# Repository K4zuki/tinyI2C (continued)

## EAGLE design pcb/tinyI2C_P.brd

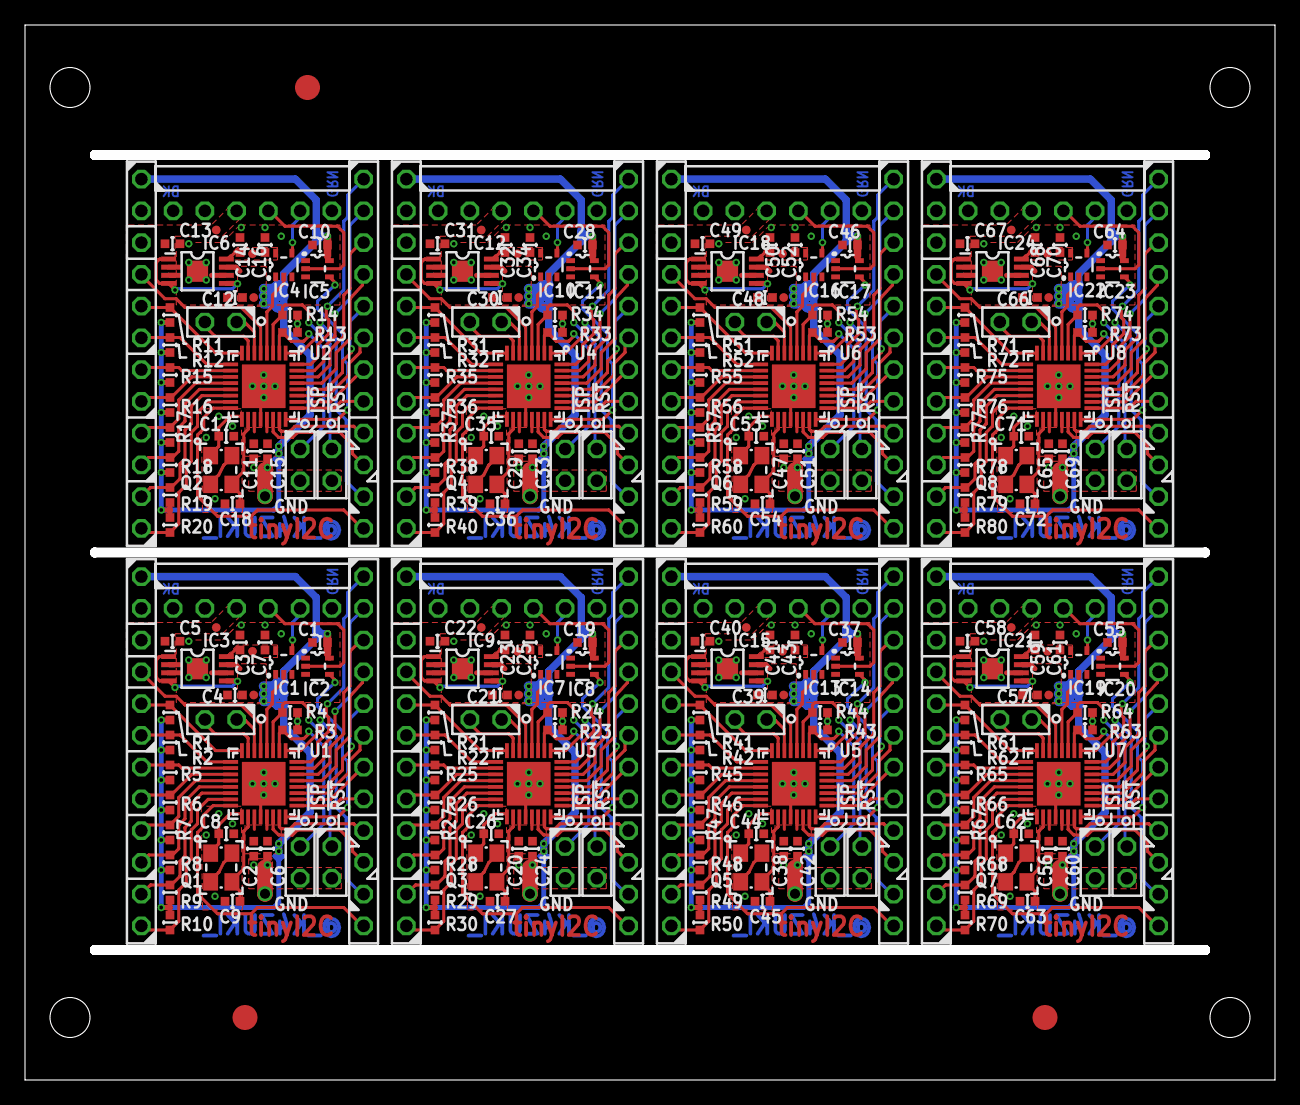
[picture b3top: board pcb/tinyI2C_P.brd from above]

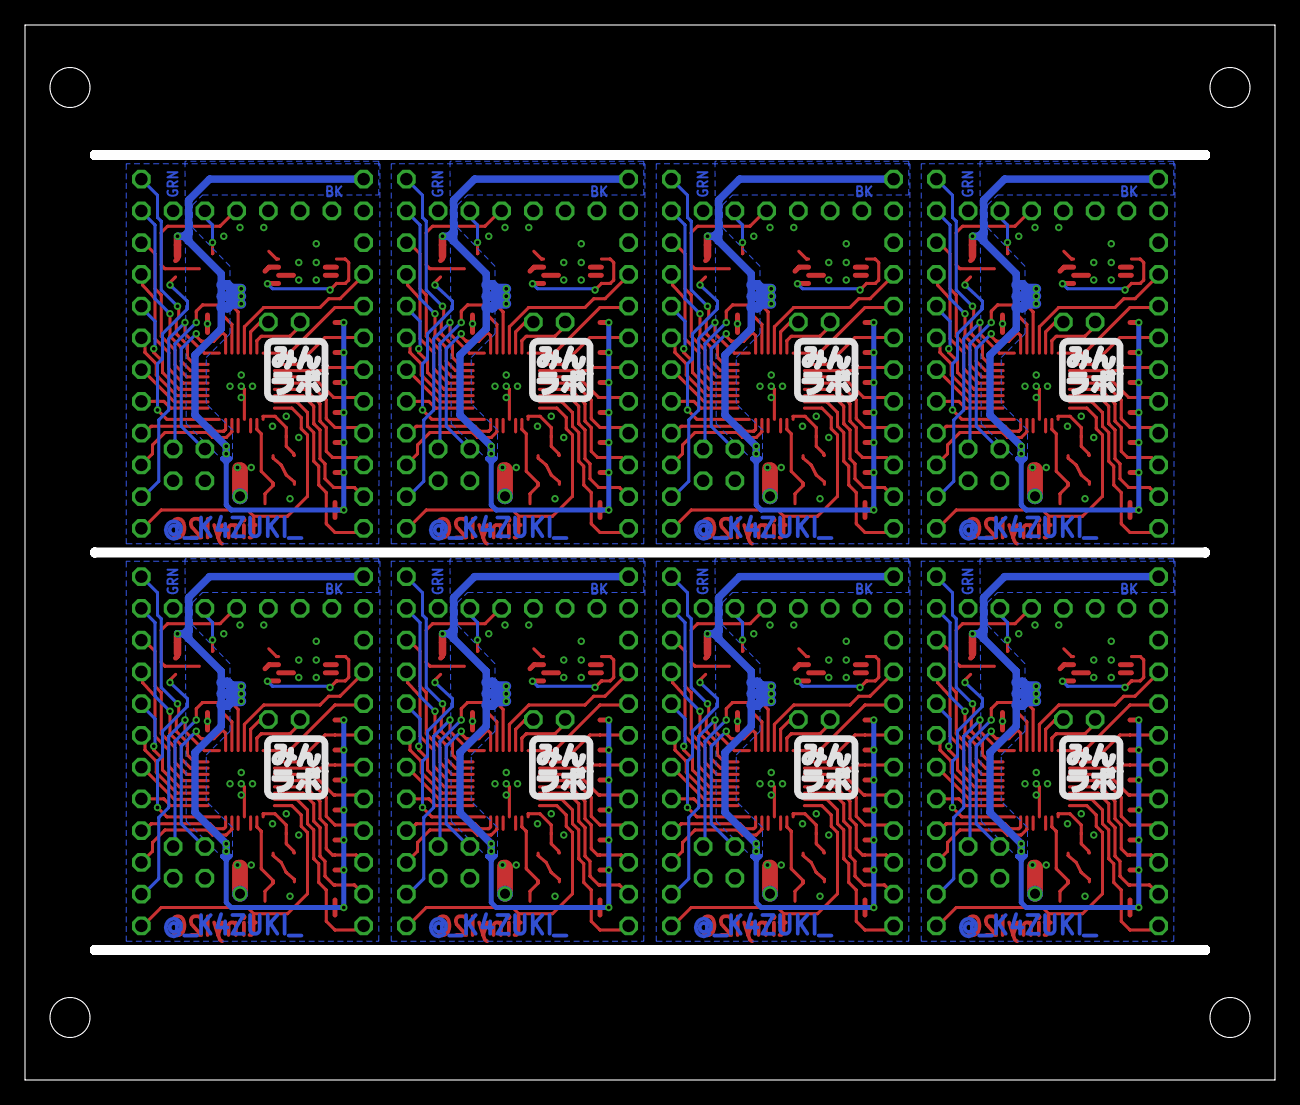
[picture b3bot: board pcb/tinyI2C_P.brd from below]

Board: 2 copper layers, 100.0 x 84.4 mm, 291 parts (16 on the bottom side), 280 nets.

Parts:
C1, C2, C6, C7, C10, C11, C15, C16, C19, C20, C24, C25, C28, C29, C33, C34, C37, C38, C42, C43, C46, C47, C51, C52, C55, C56, C60, C61, C64, C65, C69, C70: 0.1u/1005; C0402
C3, C4, C5, C12, C13, C14, C21, C22, C23, C30, C31, C32, C39, C40, C41, C48, C49, C50, C57, C58, C59, C66, C67, C68: 10u/1005; C0402
C8, C9, C17, C18, C26, C27, C35, C36, C44, C45, C53, C54, C62, C63, C71, C72: 18p/1005; C0402
I1, I2, I3, I4, I5, I6, I7, I8: ICON_MINLAB_5.2S; ICON_MINLAB_5.2MM
IC1, IC2, IC4, IC5, IC7, IC8, IC10, IC11, IC13, IC14, IC16, IC17, IC19, IC20, IC22, IC23: 74LVC1G125DCK; SC70-5
IC3, IC6, IC9, IC12, IC15, IC18, IC21, IC24: IC_LDO_MIC5355; IC_08_0.65_160MIL_EP
Q1, Q2, Q3, Q4, Q5, Q6, Q7, Q8: 12MHz; NX3225
R1, R2, R11, R12, R21, R22, R31, R32, R41, R42, R51, R52, R61, R62, R71, R72: 220/1005; C0402
R3, R4, R5, R6, R7, R8, R9, R10, R13, R14, R15, R16, R17, R18, R19, R20, R23, R24, R25, R26, R27, R28, R29, R30, R33, R34, R35, R36, R37, R38, R39, R40, R43, R44, R45, R46, R47, R48, R49, R50, R53, R54, R55, R56, R57, R58, R59, R60, R63, R64, R65, R66, R67, R68, R69, R70, R73, R74, R75, R76, R77, R78, R79, R80: 10k/1005; C0402
TP1, TP2, TP6, TP9, TP10, TP12, TP14, TP15, TP17, TP19, TP20, TP22, TP24, TP25, TP27, TP29, TP30, TP32, TP34, TP35, TP37, TP39, TP40, TP42: TPTP07R; TP07R
TP3, TP7, TP11, TP13, TP16, TP18, TP21, TP23, TP26, TP28, TP31, TP33, TP36, TP38, TP41, TP43: TPB1,27; B1,27
TP4, TP5, TP8: TPTP20R; TP20R
U1, U2, U3, U4, U5, U6, U7, U8: LPC824M201JHI33; HVQFN33
X1, X2, X8, X9, X14, X15, X20, X21, X26, X27, X32, X33, X38, X39, X44, X45: TSW-112-02-S-S
X3, X7, X13, X19, X25, X31, X37, X43: TSW-106-02-S-S-RA
X4, X5, X6, X10, X11, X12, X16, X17, X18, X22, X23, X24, X28, X29, X30, X34, X35, X36, X40, X41, X42, X46, X47, X48: TSW-102-02-S-S

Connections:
1.8V: C1.1, C2.1, C4.1, C6.1, IC2.5, IC3.7, R1.2, R2.2, R3.2, R4.2, R5.2, R6.2, R7.2, R8.2, R9.2, R10.2, TP2.TP, U1.19, U1.21, X1.1
1.8V1: C10.1, C11.1, C12.1, C15.1, IC5.5, IC6.7, R11.2, R12.2, R13.2, R14.2, R15.2, R16.2, R17.2, R18.2, R19.2, R20.2, TP10.TP, U2.19, U2.21, X8.1
1.8V2: C19.1, C20.1, C21.1, C24.1, IC8.5, IC9.7, R21.2, R22.2, R23.2, R24.2, R25.2, R26.2, R27.2, R28.2, R29.2, R30.2, TP15.TP, U3.19, U3.21, X14.1
1.8V3: C28.1, C29.1, C30.1, C33.1, IC11.5, IC12.7, R31.2, R32.2, R33.2, R34.2, R35.2, R36.2, R37.2, R38.2, R39.2, R40.2, TP20.TP, U4.19, U4.21, X20.1
1.8V4: C37.1, C38.1, C39.1, C42.1, IC14.5, IC15.7, R41.2, R42.2, R43.2, R44.2, R45.2, R46.2, R47.2, R48.2, R49.2, R50.2, TP25.TP, U5.19, U5.21, X26.1
1.8V5: C46.1, C47.1, C48.1, C51.1, IC17.5, IC18.7, R51.2, R52.2, R53.2, R54.2, R55.2, R56.2, R57.2, R58.2, R59.2, R60.2, TP30.TP, U6.19, U6.21, X32.1
1.8V6: C55.1, C56.1, C57.1, C60.1, IC20.5, IC21.7, R61.2, R62.2, R63.2, R64.2, R65.2, R66.2, R67.2, R68.2, R69.2, R70.2, TP35.TP, U7.19, U7.21, X38.1
1.8V7: C64.1, C65.1, C66.1, C69.1, IC23.5, IC24.7, R71.2, R72.2, R73.2, R74.2, R75.2, R76.2, R77.2, R78.2, R79.2, R80.2, TP40.TP, U8.19, U8.21, X44.1
3.3V: C3.1, C7.1, IC1.5, IC3.8, TP6.TP
3.3V1: C14.1, C16.1, IC4.5, IC6.8, TP12.TP
3.3V2: C23.1, C25.1, IC7.5, IC9.8, TP17.TP
3.3V3: C32.1, C34.1, IC10.5, IC12.8, TP22.TP
3.3V4: C41.1, C43.1, IC13.5, IC15.8, TP27.TP
3.3V5: C50.1, C52.1, IC16.5, IC18.8, TP32.TP
3.3V6: C59.1, C61.1, IC19.5, IC21.8, TP37.TP
3.3V7: C68.1, C70.1, IC22.5, IC24.8, TP42.TP
5V: C5.1, IC3.1, IC3.4, IC3.5, TP1.TP, X1.3, X3.3
5V1: C13.1, IC6.1, IC6.4, IC6.5, TP9.TP, X7.3, X8.3
5V2: C22.1, IC9.1, IC9.4, IC9.5, TP14.TP, X13.3, X14.3
5V3: C31.1, IC12.1, IC12.4, IC12.5, TP19.TP, X19.3, X20.3
5V4: C40.1, IC15.1, IC15.4, IC15.5, TP24.TP, X25.3, X26.3
5V5: C49.1, IC18.1, IC18.4, IC18.5, TP29.TP, X31.3, X32.3
5V6: C58.1, IC21.1, IC21.4, IC21.5, TP34.TP, X37.3, X38.3
5V7: C67.1, IC24.1, IC24.4, IC24.5, TP39.TP, X43.3, X44.3
!ISP!: R3.1, U1.2, X6.1
!ISP!1: R13.1, U2.2, X12.1
!ISP!2: R23.1, U3.2, X18.1
!ISP!3: R33.1, U4.2, X24.1
!ISP!4: R43.1, U5.2, X30.1
!ISP!5: R53.1, U6.2, X36.1
!ISP!6: R63.1, U7.2, X42.1
!ISP!7: R73.1, U8.2, X48.1
!RESET!: R4.1, U1.3, X4.1
!RESET!1: R14.1, U2.3, X10.1
!RESET!2: R24.1, U3.3, X16.1
!RESET!3: R34.1, U4.3, X22.1
!RESET!4: R44.1, U5.3, X28.1
!RESET!5: R54.1, U6.3, X34.1
!RESET!6: R64.1, U7.3, X40.1
!RESET!7: R74.1, U8.3, X46.1
GND: C1.2, C2.2, C3.2, C4.2, C5.2, C6.2, C7.2, C8.2, C9.2, IC1.1, IC1.3, IC2.1, IC2.3, IC3.2, IC3.3, IC3.6, IC3.EXP, Q1.2, Q1.4, TP3.TP, TP7.TP, U1.20, U1.EXP, X1.2, X3.1, X4.2, X6.2
GND1: C10.2, C11.2, C12.2, C13.2, C14.2, C15.2, C16.2, C17.2, C18.2, IC4.1, IC4.3, IC5.1, IC5.3, IC6.2, IC6.3, IC6.6, IC6.EXP, Q2.2, Q2.4, TP11.TP, TP13.TP, U2.20, U2.EXP, X7.1, X8.2, X10.2, X12.2
GND2: C19.2, C20.2, C21.2, C22.2, C23.2, C24.2, C25.2, C26.2, C27.2, IC7.1, IC7.3, IC8.1, IC8.3, IC9.2, IC9.3, IC9.6, IC9.EXP, Q3.2, Q3.4, TP16.TP, TP18.TP, U3.20, U3.EXP, X13.1, X14.2, X16.2, X18.2
GND3: C28.2, C29.2, C30.2, C31.2, C32.2, C33.2, C34.2, C35.2, C36.2, IC10.1, IC10.3, IC11.1, IC11.3, IC12.2, IC12.3, IC12.6, IC12.EXP, Q4.2, Q4.4, TP21.TP, TP23.TP, U4.20, U4.EXP, X19.1, X20.2, X22.2, X24.2
GND4: C37.2, C38.2, C39.2, C40.2, C41.2, C42.2, C43.2, C44.2, C45.2, IC13.1, IC13.3, IC14.1, IC14.3, IC15.2, IC15.3, IC15.6, IC15.EXP, Q5.2, Q5.4, TP26.TP, TP28.TP, U5.20, U5.EXP, X25.1, X26.2, X28.2, X30.2
GND5: C46.2, C47.2, C48.2, C49.2, C50.2, C51.2, C52.2, C53.2, C54.2, IC16.1, IC16.3, IC17.1, IC17.3, IC18.2, IC18.3, IC18.6, IC18.EXP, Q6.2, Q6.4, TP31.TP, TP33.TP, U6.20, U6.EXP, X31.1, X32.2, X34.2, X36.2
GND6: C55.2, C56.2, C57.2, C58.2, C59.2, C60.2, C61.2, C62.2, C63.2, IC19.1, IC19.3, IC20.1, IC20.3, IC21.2, IC21.3, IC21.6, IC21.EXP, Q7.2, Q7.4, TP36.TP, TP38.TP, U7.20, U7.EXP, X37.1, X38.2, X40.2, X42.2
GND7: C64.2, C65.2, C66.2, C67.2, C68.2, C69.2, C70.2, C71.2, C72.2, IC22.1, IC22.3, IC23.1, IC23.3, IC24.2, IC24.3, IC24.6, IC24.EXP, Q8.2, Q8.4, TP41.TP, TP43.TP, U8.20, U8.EXP, X43.1, X44.2, X46.2, X48.2
GPIO00: U1.32, X2.1
GPIO01: U1.31, X2.2
GPIO02: U1.30, X2.3
GPIO03: U1.29, X2.4
GPIO04: U1.28, X2.5
GPIO05: U1.27, X2.6
GPIO06: U1.26, X2.7
GPIO07: U1.25, X2.8
GPIO08: U2.5, X8.4
GPIO09: R15.1, U2.10, X8.7
GPIO10: R10.1, U1.15, X1.12
GPIO11: R9.1, U1.14, X1.11
GPIO12: R8.1, U1.13, X1.10
GPIO13: R7.1, U1.12, X1.9
GPIO14: R6.1, U1.11, X1.8
GPIO15: R5.1, U1.10, X1.7
GPIO16: U1.5, X1.4
GPIO17: R16.1, U2.11, X8.8
GPIO18: R17.1, U2.12, X8.9
GPIO19: R18.1, U2.13, X8.10
GPIO20: R19.1, U2.14, X8.11
GPIO21: R20.1, U2.15, X8.12
GPIO22: U2.25, X9.8
GPIO23: U2.26, X9.7
GPIO24: U2.27, X9.6
GPIO25: U2.28, X9.5
GPIO26: U2.29, X9.4
GPIO27: U2.30, X9.3
GPIO28: U2.31, X9.2
GPIO29: U2.32, X9.1
GPIO30: U3.5, X14.4
GPIO31: R25.1, U3.10, X14.7
GPIO32: R26.1, U3.11, X14.8
GPIO33: R27.1, U3.12, X14.9
GPIO34: R28.1, U3.13, X14.10
GPIO35: R29.1, U3.14, X14.11
GPIO36: R30.1, U3.15, X14.12
GPIO37: U3.25, X15.8
GPIO38: U3.26, X15.7
GPIO39: U3.27, X15.6
GPIO40: U3.28, X15.5
GPIO41: U3.29, X15.4
GPIO42: U3.30, X15.3
GPIO43: U3.31, X15.2
GPIO44: U3.32, X15.1
GPIO45: U4.5, X20.4
GPIO46: R35.1, U4.10, X20.7
GPIO47: R36.1, U4.11, X20.8
GPIO48: R37.1, U4.12, X20.9
GPIO49: R38.1, U4.13, X20.10
GPIO50: R39.1, U4.14, X20.11
GPIO51: R40.1, U4.15, X20.12
GPIO52: U4.25, X21.8
GPIO53: U4.26, X21.7
GPIO54: U4.27, X21.6
GPIO55: U4.28, X21.5
GPIO56: U4.29, X21.4
GPIO57: U4.30, X21.3
GPIO58: U4.31, X21.2
GPIO59: U4.32, X21.1
GPIO60: U5.5, X26.4
GPIO61: R45.1, U5.10, X26.7
GPIO62: R46.1, U5.11, X26.8
GPIO63: R47.1, U5.12, X26.9
GPIO64: R48.1, U5.13, X26.10
GPIO65: R49.1, U5.14, X26.11
GPIO66: R50.1, U5.15, X26.12
GPIO67: U5.25, X27.8
GPIO68: U5.26, X27.7
GPIO69: U5.27, X27.6
GPIO70: U5.28, X27.5
GPIO71: U5.29, X27.4
GPIO72: U5.30, X27.3
GPIO73: U5.31, X27.2
GPIO74: U5.32, X27.1
GPIO75: U6.5, X32.4
GPIO76: R55.1, U6.10, X32.7
GPIO77: R56.1, U6.11, X32.8
GPIO78: R57.1, U6.12, X32.9
GPIO79: R58.1, U6.13, X32.10
GPIO80: R59.1, U6.14, X32.11
GPIO81: R60.1, U6.15, X32.12
GPIO82: U6.25, X33.8
GPIO83: U6.26, X33.7
GPIO84: U6.27, X33.6
GPIO85: U6.28, X33.5
GPIO86: U6.29, X33.4
GPIO87: U6.30, X33.3
GPIO88: U6.31, X33.2
GPIO89: U6.32, X33.1
GPIO90: U7.5, X38.4
GPIO91: R65.1, U7.10, X38.7
GPIO92: R66.1, U7.11, X38.8
GPIO93: R67.1, U7.12, X38.9
GPIO94: R68.1, U7.13, X38.10
GPIO95: R69.1, U7.14, X38.11
GPIO96: R70.1, U7.15, X38.12
GPIO97: U7.25, X39.8
GPIO98: U7.26, X39.7
GPIO99: U7.27, X39.6
GPIO100: U7.28, X39.5
GPIO101: U7.29, X39.4
GPIO102: U7.30, X39.3
GPIO103: U7.31, X39.2
GPIO104: U7.32, X39.1
GPIO105: U8.5, X44.4
GPIO106: R75.1, U8.10, X44.7
GPIO107: R76.1, U8.11, X44.8
GPIO108: R77.1, U8.12, X44.9
GPIO109: R78.1, U8.13, X44.10
GPIO110: R79.1, U8.14, X44.11
GPIO111: R80.1, U8.15, X44.12
GPIO112: U8.25, X45.8
GPIO113: U8.26, X45.7
GPIO114: U8.27, X45.6
GPIO115: U8.28, X45.5
GPIO116: U8.29, X45.4
GPIO117: U8.30, X45.3
GPIO118: U8.31, X45.2
GPIO119: U8.32, X45.1
I2C_SCL: R2.1, U1.9, X1.6
I2C_SCL1: R12.1, U2.9, X8.6
I2C_SCL2: R22.1, U3.9, X14.6
I2C_SCL3: R32.1, U4.9, X20.6
I2C_SCL4: R42.1, U5.9, X26.6
I2C_SCL5: R52.1, U6.9, X32.6
I2C_SCL6: R62.1, U7.9, X38.6
I2C_SCL7: R72.1, U8.9, X44.6
I2C_SDA: R1.1, U1.8, X1.5
I2C_SDA1: R11.1, U2.8, X8.5
I2C_SDA2: R21.1, U3.8, X14.5
I2C_SDA3: R31.1, U4.8, X20.5
I2C_SDA4: R41.1, U5.8, X26.5
I2C_SDA5: R51.1, U6.8, X32.5
I2C_SDA6: R61.1, U7.8, X38.5
I2C_SDA7: R71.1, U8.8, X44.5
unnamed: C8.1, Q1.1, U1.17
unnamed: C17.1, Q2.1, U2.17
unnamed: C9.1, Q1.3, U1.18
unnamed: C18.1, Q2.3, U2.18
unnamed: C26.1, Q3.1, U3.17
unnamed: C27.1, Q3.3, U3.18
unnamed: C35.1, Q4.1, U4.17
unnamed: C36.1, Q4.3, U4.18
unnamed: C44.1, Q5.1, U5.17
unnamed: C45.1, Q5.3, U5.18
unnamed: C53.1, Q6.1, U6.17
unnamed: C54.1, Q6.3, U6.18
unnamed: C62.1, Q7.1, U7.17
unnamed: C63.1, Q7.3, U7.18
unnamed: C71.1, Q8.1, U8.17
unnamed: C72.1, Q8.3, U8.18
RX<-: IC1.4, X3.5
RX<-1: IC4.4, X7.5
RX<-2: IC7.4, X13.5
RX<-3: IC10.4, X19.5
RX<-4: IC13.4, X25.5
RX<-5: IC16.4, X31.5
RX<-6: IC19.4, X37.5
RX<-7: IC22.4, X43.5
SPI_CS: U1.16, X2.12
SPI_CS1: U2.16, X9.12
SPI_CS2: U3.16, X15.12
SPI_CS3: U4.16, X21.12
SPI_CS4: U5.16, X27.12
SPI_CS5: U6.16, X33.12
SPI_CS6: U7.16, X39.12
SPI_CS7: U8.16, X45.12
SPI_MISO: U1.22, X2.10
SPI_MISO1: U2.22, X9.10
SPI_MISO2: U3.22, X15.10
SPI_MISO3: U4.22, X21.10
SPI_MISO4: U5.22, X27.10
SPI_MISO5: U6.22, X33.10
SPI_MISO6: U7.22, X39.10
SPI_MISO7: U8.22, X45.10
SPI_MOSI: U1.23, X2.9
SPI_MOSI1: U2.23, X9.9
SPI_MOSI2: U3.23, X15.9
SPI_MOSI3: U4.23, X21.9
SPI_MOSI4: U5.23, X27.9
SPI_MOSI5: U6.23, X33.9
SPI_MOSI6: U7.23, X39.9
SPI_MOSI7: U8.23, X45.9
SPI_SCK: U1.1, X2.11
SPI_SCK1: U2.1, X9.11
SPI_SCK2: U3.1, X15.11
SPI_SCK3: U4.1, X21.11
SPI_SCK4: U5.1, X27.11
SPI_SCK5: U6.1, X33.11
SPI_SCK6: U7.1, X39.11
SPI_SCK7: U8.1, X45.11
SWCLK: U1.6, X5.1
SWCLK1: U2.6, X11.1
SWCLK2: U3.6, X17.1
SWCLK3: U4.6, X23.1
SWCLK4: U5.6, X29.1
SWCLK5: U6.6, X35.1
SWCLK6: U7.6, X41.1
SWCLK7: U8.6, X47.1
SWDIO: U1.7, X5.2
SWDIO1: U2.7, X11.2
SWDIO2: U3.7, X17.2
SWDIO3: U4.7, X23.2
SWDIO4: U5.7, X29.2
SWDIO5: U6.7, X35.2
SWDIO6: U7.7, X41.2
SWDIO7: U8.7, X47.2
TGT_RX: IC2.4, U1.24
TGT_RX1: IC5.4, U2.24
TGT_RX2: IC8.4, U3.24
TGT_RX3: IC11.4, U4.24
TGT_RX4: IC14.4, U5.24
TGT_RX5: IC17.4, U6.24
TGT_RX6: IC20.4, U7.24
TGT_RX7: IC23.4, U8.24
TGT_TX: IC1.2, U1.4
TGT_TX1: IC4.2, U2.4
TGT_TX2: IC7.2, U3.4
TGT_TX3: IC10.2, U4.4
TGT_TX4: IC13.2, U5.4
TGT_TX5: IC16.2, U6.4
TGT_TX6: IC19.2, U7.4
TGT_TX7: IC22.2, U8.4
TX->: IC2.2, X3.4
TX->1: IC5.2, X7.4
TX->2: IC8.2, X13.4
TX->3: IC11.2, X19.4
TX->4: IC14.2, X25.4
TX->5: IC17.2, X31.4
TX->6: IC20.2, X37.4
TX->7: IC23.2, X43.4

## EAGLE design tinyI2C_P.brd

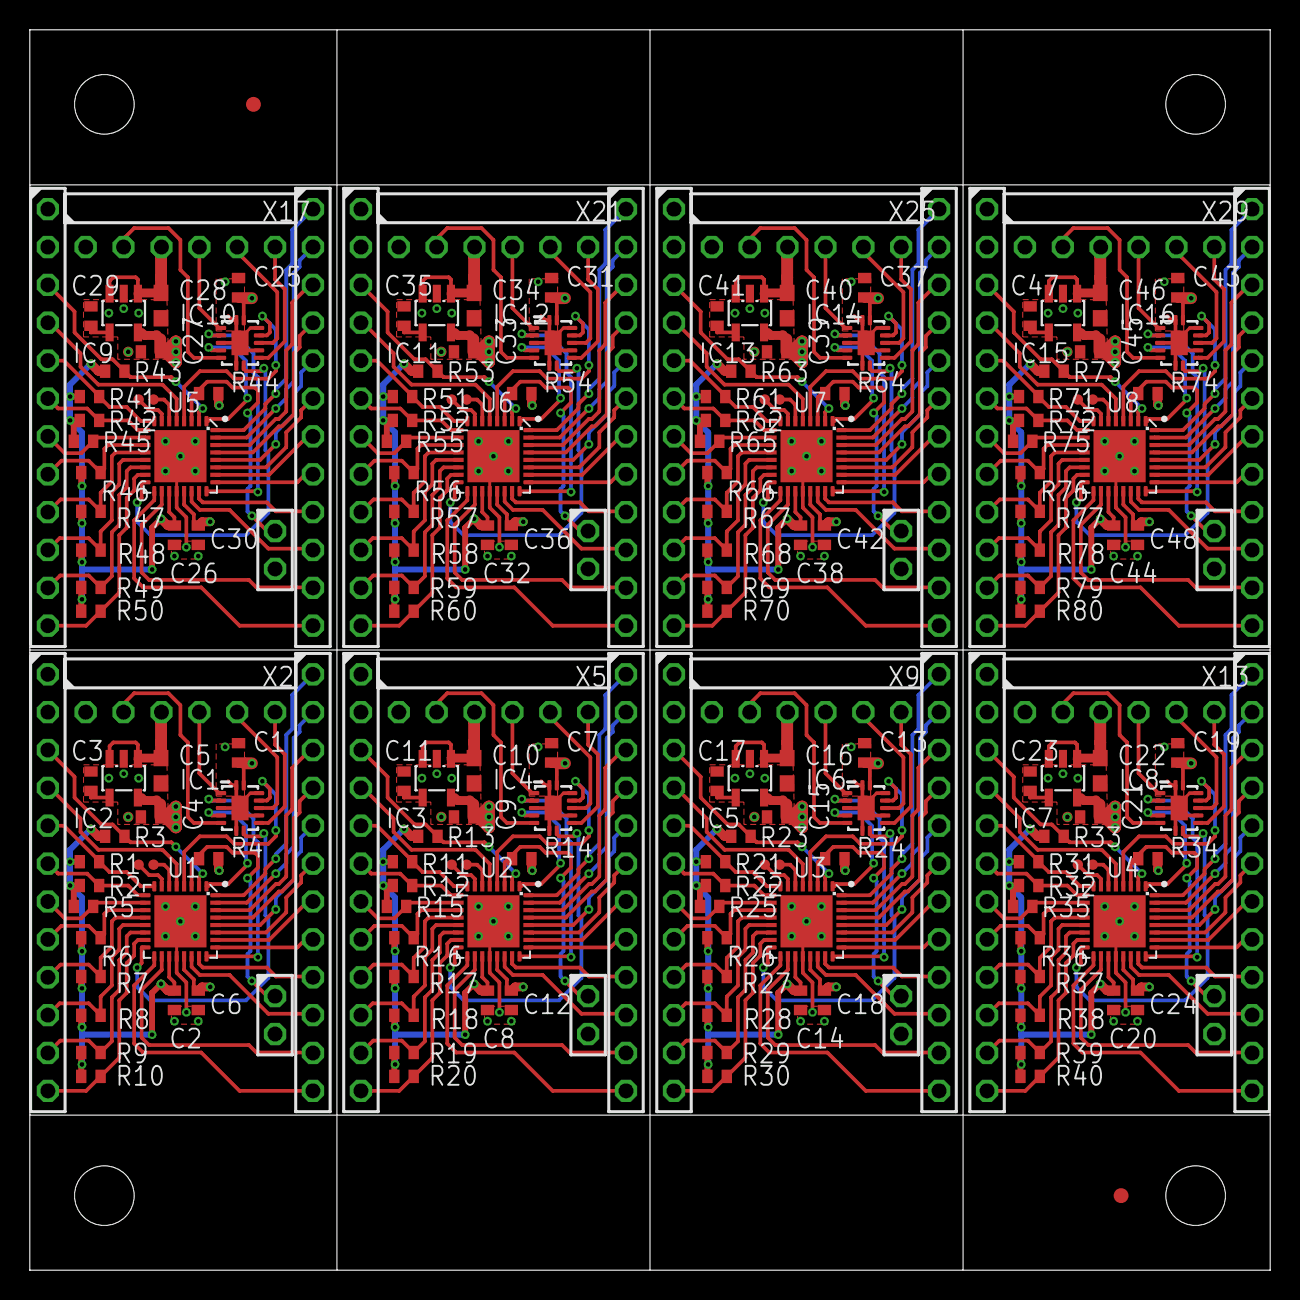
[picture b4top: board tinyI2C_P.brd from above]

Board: 2 copper layers, 83.2 x 83.2 mm, 226 parts (0 on the bottom side), 296 nets.

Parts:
C1, C2, C3, C4, C6, C7, C8, C9, C11, C12, C13, C14, C15, C17, C18, C19, C20, C21, C23, C24, C25, C26, C27, C29, C30, C31, C32, C33, C35, C36, C37, C38, C39, C41, C42, C43, C44, C45, C47, C48: 1005; C1005
C5, C10, C16, C22, C28, C34, C40, C46: 1608; C1608
IC1, IC4, IC6, IC8, IC10, IC12, IC14, IC16: 74ABT125BQ; DHVQFN14
IC2, IC3, IC5, IC7, IC9, IC11, IC13, IC15: TPS76318; SOT23-DBV
R1, R2, R11, R12, R21, R22, R31, R32, R41, R42, R51, R52, R61, R62, R71, R72: 220/1005; R1005
R3, R4, R5, R6, R7, R8, R9, R10, R13, R14, R15, R16, R17, R18, R19, R20, R23, R24, R25, R26, R27, R28, R29, R30, R33, R34, R35, R36, R37, R38, R39, R40, R43, R44, R45, R46, R47, R48, R49, R50, R53, R54, R55, R56, R57, R58, R59, R60, R63, R64, R65, R66, R67, R68, R69, R70, R73, R74, R75, R76, R77, R78, R79, R80: 10k/1005; R1005
TP1, TP2, TP3, TP6, TP7, TP8, TP9, TP10, TP11, TP12, TP13, TP14, TP15, TP16, TP17, TP18, TP19, TP20, TP21, TP22, TP23, TP24, TP25, TP26, TP27, TP28, TP29, TP30, TP31, TP32, TP33, TP34, TP35, TP36, TP37, TP38, TP39, TP40, TP41, TP42: TPTP07R; TP07R
TP4, TP5: TPTP10R; TP10R
U1, U2, U3, U4, U5, U6, U7, U8: LPC824M201JHI33; HVQFN33
X1, X3, X6, X7, X10, X11, X14, X15, X18, X19, X22, X23, X26, X27, X30, X31: TSW-112-02-S-S
X2, X5, X9, X13, X17, X21, X25, X29: TSW-106-02-S-S-RA
X4, X8, X12, X16, X20, X24, X28, X32: TSW-102-02-S-S

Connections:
1.8V: C1.1, C2.1, C4.1, C6.1, IC1.14, IC2.5, R1.2, R2.2, R3.2, R4.2, R5.2, R6.2, R7.2, R8.2, R9.2, R10.2, TP2.TP, U1.19, U1.21, X1.1
1.8V1: C7.1, C8.1, C9.1, C12.1, IC3.5, IC4.14, R11.2, R12.2, R13.2, R14.2, R15.2, R16.2, R17.2, R18.2, R19.2, R20.2, TP7.TP, U2.19, U2.21, X6.1
1.8V2: C13.1, C14.1, C15.1, C18.1, IC5.5, IC6.14, R21.2, R22.2, R23.2, R24.2, R25.2, R26.2, R27.2, R28.2, R29.2, R30.2, TP14.TP, U3.19, U3.21, X10.1
1.8V3: C19.1, C20.1, C21.1, C24.1, IC7.5, IC8.14, R31.2, R32.2, R33.2, R34.2, R35.2, R36.2, R37.2, R38.2, R39.2, R40.2, TP19.TP, U4.19, U4.21, X14.1
1.8V4: C25.1, C26.1, C27.1, C30.1, IC9.5, IC10.14, R41.2, R42.2, R43.2, R44.2, R45.2, R46.2, R47.2, R48.2, R49.2, R50.2, TP24.TP, U5.19, U5.21, X18.1
1.8V5: C31.1, C32.1, C33.1, C36.1, IC11.5, IC12.14, R51.2, R52.2, R53.2, R54.2, R55.2, R56.2, R57.2, R58.2, R59.2, R60.2, TP29.TP, U6.19, U6.21, X22.1
1.8V6: C37.1, C38.1, C39.1, C42.1, IC13.5, IC14.14, R61.2, R62.2, R63.2, R64.2, R65.2, R66.2, R67.2, R68.2, R69.2, R70.2, TP34.TP, U7.19, U7.21, X26.1
1.8V7: C43.1, C44.1, C45.1, C48.1, IC15.5, IC16.14, R71.2, R72.2, R73.2, R74.2, R75.2, R76.2, R77.2, R78.2, R79.2, R80.2, TP39.TP, U8.19, U8.21, X30.1
5V: C5.1, IC2.1, IC2.3, TP1.TP, X2.3
5V1: C10.1, IC3.1, IC3.3, TP6.TP, X5.3
5V2: C16.1, IC5.1, IC5.3, TP13.TP, X9.3
5V3: C22.1, IC7.1, IC7.3, TP18.TP, X13.3
5V4: C28.1, IC9.1, IC9.3, TP23.TP, X17.3
5V5: C34.1, IC11.1, IC11.3, TP28.TP, X21.3
5V6: C40.1, IC13.1, IC13.3, TP33.TP, X25.3
5V7: C46.1, IC15.1, IC15.3, TP38.TP, X29.3
!ISP!: R3.1, U1.2, X1.3
!ISP!1: R13.1, U2.2, X6.3
!ISP!2: R23.1, U3.2, X10.3
!ISP!3: R33.1, U4.2, X14.3
!ISP!4: R43.1, U5.2, X18.3
!ISP!5: R53.1, U6.2, X22.3
!ISP!6: R63.1, U7.2, X26.3
!ISP!7: R73.1, U8.2, X30.3
!RESET!: R4.1, U1.3, X4.1
!RESET!1: R14.1, U2.3, X8.1
!RESET!2: R24.1, U3.3, X12.1
!RESET!3: R34.1, U4.3, X16.1
!RESET!4: R44.1, U5.3, X20.1
!RESET!5: R54.1, U6.3, X24.1
!RESET!6: R64.1, U7.3, X28.1
!RESET!7: R74.1, U8.3, X32.1
CTS<-: IC1.6, X2.2
CTS<-1: IC4.6, X5.2
CTS<-2: IC6.6, X9.2
CTS<-3: IC8.6, X13.2
CTS<-4: IC10.6, X17.2
CTS<-5: IC12.6, X21.2
CTS<-6: IC14.6, X25.2
CTS<-7: IC16.6, X29.2
GND: C1.2, C2.2, C3.2, C4.2, C5.2, C6.2, IC1.1, IC1.4, IC1.7, IC1.10, IC1.13, IC1.EXP, IC2.2, TP3.TP, U1.20, U1.EXP, X1.2, X2.1, X4.2
GND1: C7.2, C8.2, C9.2, C10.2, C11.2, C12.2, IC3.2, IC4.1, IC4.4, IC4.7, IC4.10, IC4.13, IC4.EXP, TP12.TP, U2.20, U2.EXP, X5.1, X6.2, X8.2
GND2: C13.2, C14.2, C15.2, C16.2, C17.2, C18.2, IC5.2, IC6.1, IC6.4, IC6.7, IC6.10, IC6.13, IC6.EXP, TP17.TP, U3.20, U3.EXP, X9.1, X10.2, X12.2
GND3: C19.2, C20.2, C21.2, C22.2, C23.2, C24.2, IC7.2, IC8.1, IC8.4, IC8.7, IC8.10, IC8.13, IC8.EXP, TP22.TP, U4.20, U4.EXP, X13.1, X14.2, X16.2
GND4: C25.2, C26.2, C27.2, C28.2, C29.2, C30.2, IC9.2, IC10.1, IC10.4, IC10.7, IC10.10, IC10.13, IC10.EXP, TP27.TP, U5.20, U5.EXP, X17.1, X18.2, X20.2
GND5: C31.2, C32.2, C33.2, C34.2, C35.2, C36.2, IC11.2, IC12.1, IC12.4, IC12.7, IC12.10, IC12.13, IC12.EXP, TP32.TP, U6.20, U6.EXP, X21.1, X22.2, X24.2
GND6: C37.2, C38.2, C39.2, C40.2, C41.2, C42.2, IC13.2, IC14.1, IC14.4, IC14.7, IC14.10, IC14.13, IC14.EXP, TP37.TP, U7.20, U7.EXP, X25.1, X26.2, X28.2
GND7: C43.2, C44.2, C45.2, C46.2, C47.2, C48.2, IC15.2, IC16.1, IC16.4, IC16.7, IC16.10, IC16.13, IC16.EXP, TP42.TP, U8.20, U8.EXP, X29.1, X30.2, X32.2
GPIO00: U1.32, X3.1
GPIO01: U1.31, X3.2
GPIO02: U1.30, X3.3
GPIO03: U1.29, X3.4
GPIO04: U1.28, X3.5
GPIO05: U1.27, X3.6
GPIO06: U1.26, X3.7
GPIO07: U1.25, X3.8
GPIO08: U2.5, X6.4
GPIO09: R15.1, U2.10, X6.7
GPIO10: R10.1, U1.15, X1.12
GPIO11: R9.1, U1.14, X1.11
GPIO12: R8.1, U1.13, X1.10
GPIO13: R7.1, U1.12, X1.9
GPIO14: R6.1, U1.11, X1.8
GPIO15: R5.1, U1.10, X1.7
GPIO16: U1.5, X1.4
GPIO17: R16.1, U2.11, X6.8
GPIO18: R17.1, U2.12, X6.9
GPIO19: R18.1, U2.13, X6.10
GPIO20: R19.1, U2.14, X6.11
GPIO21: R20.1, U2.15, X6.12
GPIO22: U2.25, X7.8
GPIO23: U2.26, X7.7
GPIO24: U2.27, X7.6
GPIO25: U2.28, X7.5
GPIO26: U2.29, X7.4
GPIO27: U2.30, X7.3
GPIO28: U2.31, X7.2
GPIO29: U2.32, X7.1
GPIO30: U3.5, X10.4
GPIO31: R25.1, U3.10, X10.7
GPIO32: R26.1, U3.11, X10.8
GPIO33: R27.1, U3.12, X10.9
GPIO34: R28.1, U3.13, X10.10
GPIO35: R29.1, U3.14, X10.11
GPIO36: R30.1, U3.15, X10.12
GPIO37: U3.25, X11.8
GPIO38: U3.26, X11.7
GPIO39: U3.27, X11.6
GPIO40: U3.28, X11.5
GPIO41: U3.29, X11.4
GPIO42: U3.30, X11.3
GPIO43: U3.31, X11.2
GPIO44: U3.32, X11.1
GPIO45: U4.5, X14.4
GPIO46: R35.1, U4.10, X14.7
GPIO47: R36.1, U4.11, X14.8
GPIO48: R37.1, U4.12, X14.9
GPIO49: R38.1, U4.13, X14.10
GPIO50: R39.1, U4.14, X14.11
GPIO51: R40.1, U4.15, X14.12
GPIO52: U4.25, X15.8
GPIO53: U4.26, X15.7
GPIO54: U4.27, X15.6
GPIO55: U4.28, X15.5
GPIO56: U4.29, X15.4
GPIO57: U4.30, X15.3
GPIO58: U4.31, X15.2
GPIO59: U4.32, X15.1
GPIO60: U5.5, X18.4
GPIO61: R45.1, U5.10, X18.7
GPIO62: R46.1, U5.11, X18.8
GPIO63: R47.1, U5.12, X18.9
GPIO64: R48.1, U5.13, X18.10
GPIO65: R49.1, U5.14, X18.11
GPIO66: R50.1, U5.15, X18.12
GPIO67: U5.25, X19.8
GPIO68: U5.26, X19.7
GPIO69: U5.27, X19.6
GPIO70: U5.28, X19.5
GPIO71: U5.29, X19.4
GPIO72: U5.30, X19.3
GPIO73: U5.31, X19.2
GPIO74: U5.32, X19.1
GPIO75: U6.5, X22.4
GPIO76: R55.1, U6.10, X22.7
GPIO77: R56.1, U6.11, X22.8
GPIO78: R57.1, U6.12, X22.9
GPIO79: R58.1, U6.13, X22.10
GPIO80: R59.1, U6.14, X22.11
GPIO81: R60.1, U6.15, X22.12
GPIO82: U6.25, X23.8
GPIO83: U6.26, X23.7
GPIO84: U6.27, X23.6
GPIO85: U6.28, X23.5
GPIO86: U6.29, X23.4
GPIO87: U6.30, X23.3
GPIO88: U6.31, X23.2
GPIO89: U6.32, X23.1
GPIO90: U7.5, X26.4
GPIO91: R65.1, U7.10, X26.7
GPIO92: R66.1, U7.11, X26.8
GPIO93: R67.1, U7.12, X26.9
GPIO94: R68.1, U7.13, X26.10
GPIO95: R69.1, U7.14, X26.11
GPIO96: R70.1, U7.15, X26.12
GPIO97: U7.25, X27.8
GPIO98: U7.26, X27.7
GPIO99: U7.27, X27.6
GPIO100: U7.28, X27.5
GPIO101: U7.29, X27.4
GPIO102: U7.30, X27.3
GPIO103: U7.31, X27.2
GPIO104: U7.32, X27.1
GPIO105: U8.5, X30.4
GPIO106: R75.1, U8.10, X30.7
GPIO107: R76.1, U8.11, X30.8
GPIO108: R77.1, U8.12, X30.9
GPIO109: R78.1, U8.13, X30.10
GPIO110: R79.1, U8.14, X30.11
GPIO111: R80.1, U8.15, X30.12
GPIO112: U8.25, X31.8
GPIO113: U8.26, X31.7
GPIO114: U8.27, X31.6
GPIO115: U8.28, X31.5
GPIO116: U8.29, X31.4
GPIO117: U8.30, X31.3
GPIO118: U8.31, X31.2
GPIO119: U8.32, X31.1
I2C_SCL: R2.1, U1.9, X1.6
I2C_SCL1: R12.1, U2.9, X6.6
I2C_SCL2: R22.1, U3.9, X10.6
I2C_SCL3: R32.1, U4.9, X14.6
I2C_SCL4: R42.1, U5.9, X18.6
I2C_SCL5: R52.1, U6.9, X22.6
I2C_SCL6: R62.1, U7.9, X26.6
I2C_SCL7: R72.1, U8.9, X30.6
I2C_SDA: R1.1, U1.8, X1.5
I2C_SDA1: R11.1, U2.8, X6.5
I2C_SDA2: R21.1, U3.8, X10.5
I2C_SDA3: R31.1, U4.8, X14.5
I2C_SDA4: R41.1, U5.8, X18.5
I2C_SDA5: R51.1, U6.8, X22.5
I2C_SDA6: R61.1, U7.8, X26.5
I2C_SDA7: R71.1, U8.8, X30.5
unnamed: C3.1, IC2.4
unnamed: C11.1, IC3.4
unnamed: C17.1, IC5.4
unnamed: C23.1, IC7.4
unnamed: C29.1, IC9.4
unnamed: C35.1, IC11.4
unnamed: C41.1, IC13.4
unnamed: C47.1, IC15.4
RTS->: IC1.9, X2.6
RTS->1: IC4.9, X5.6
RTS->2: IC6.9, X9.6
RTS->3: IC8.9, X13.6
RTS->4: IC10.9, X17.6
RTS->5: IC12.9, X21.6
RTS->6: IC14.9, X25.6
RTS->7: IC16.9, X29.6
RX<-: IC1.11, X2.5
RX<-1: IC4.11, X5.5
RX<-2: IC6.11, X9.5
RX<-3: IC8.11, X13.5
RX<-4: IC10.11, X17.5
RX<-5: IC12.11, X21.5
RX<-6: IC14.11, X25.5
RX<-7: IC16.11, X29.5
SPI_CS: U1.17, X3.12
SPI_CS1: U2.17, X7.12
SPI_CS2: U3.17, X11.12
SPI_CS3: U4.17, X15.12
SPI_CS4: U5.17, X19.12
SPI_CS5: U6.17, X23.12
SPI_CS6: U7.17, X27.12
SPI_CS7: U8.17, X31.12
SPI_MISO: U1.22, X3.10
SPI_MISO1: U2.22, X7.10
SPI_MISO2: U3.22, X11.10
SPI_MISO3: U4.22, X15.10
SPI_MISO4: U5.22, X19.10
SPI_MISO5: U6.22, X23.10
SPI_MISO6: U7.22, X27.10
SPI_MISO7: U8.22, X31.10
SPI_MOSI: U1.23, X3.9
SPI_MOSI1: U2.23, X7.9
SPI_MOSI2: U3.23, X11.9
SPI_MOSI3: U4.23, X15.9
SPI_MOSI4: U5.23, X19.9
SPI_MOSI5: U6.23, X23.9
SPI_MOSI6: U7.23, X27.9
SPI_MOSI7: U8.23, X31.9
SPI_SCK: U1.18, X3.11
SPI_SCK1: U2.18, X7.11
SPI_SCK2: U3.18, X11.11
SPI_SCK3: U4.18, X15.11
SPI_SCK4: U5.18, X19.11
SPI_SCK5: U6.18, X23.11
SPI_SCK6: U7.18, X27.11
SPI_SCK7: U8.18, X31.11
SWCLK: TP8.TP, U1.6
SWCLK1: TP10.TP, U2.6
SWCLK2: TP15.TP, U3.6
SWCLK3: TP20.TP, U4.6
SWCLK4: TP25.TP, U5.6
SWCLK5: TP30.TP, U6.6
SWCLK6: TP35.TP, U7.6
SWCLK7: TP40.TP, U8.6
SWDIO: TP9.TP, U1.7
SWDIO1: TP11.TP, U2.7
SWDIO2: TP16.TP, U3.7
SWDIO3: TP21.TP, U4.7
SWDIO4: TP26.TP, U5.7
SWDIO5: TP31.TP, U6.7
SWDIO6: TP36.TP, U7.7
SWDIO7: TP41.TP, U8.7
TGT_CTS: IC1.8, U1.16
TGT_CTS1: IC4.8, U2.16
TGT_CTS2: IC6.8, U3.16
TGT_CTS3: IC8.8, U4.16
TGT_CTS4: IC10.8, U5.16
TGT_CTS5: IC12.8, U6.16
TGT_CTS6: IC14.8, U7.16
TGT_CTS7: IC16.8, U8.16
TGT_RTS: IC1.5, U1.1
TGT_RTS1: IC4.5, U2.1
TGT_RTS2: IC6.5, U3.1
TGT_RTS3: IC8.5, U4.1
TGT_RTS4: IC10.5, U5.1
TGT_RTS5: IC12.5, U6.1
TGT_RTS6: IC14.5, U7.1
TGT_RTS7: IC16.5, U8.1
TGT_RX: IC1.3, U1.24
TGT_RX1: IC4.3, U2.24
TGT_RX2: IC6.3, U3.24
TGT_RX3: IC8.3, U4.24
TGT_RX4: IC10.3, U5.24
TGT_RX5: IC12.3, U6.24
TGT_RX6: IC14.3, U7.24
TGT_RX7: IC16.3, U8.24
TGT_TX: IC1.12, U1.4
TGT_TX1: IC4.12, U2.4
TGT_TX2: IC6.12, U3.4
TGT_TX3: IC8.12, U4.4
TGT_TX4: IC10.12, U5.4
TGT_TX5: IC12.12, U6.4
TGT_TX6: IC14.12, U7.4
TGT_TX7: IC16.12, U8.4
TX->: IC1.2, X2.4
TX->1: IC4.2, X5.4
TX->2: IC6.2, X9.4
TX->3: IC8.2, X13.4
TX->4: IC10.2, X17.4
TX->5: IC12.2, X21.4
TX->6: IC14.2, X25.4
TX->7: IC16.2, X29.4

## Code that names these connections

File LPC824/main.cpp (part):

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I2C dev4(P0_24, P0_15);
*/
#else
DigitalInOut _GPIO10(P0_15);
DigitalInOut _GPIO11(P0_24);
DigitalInOut _GPIO12(P0_25);
DigitalInOut _GPIO13(P0_26);
DigitalInOut _GPIO14(P0_27);
DigitalInOut _GPIO15(P0_16);
DigitalInOut _GPIO16(P0_28);
DigitalInOut _GPIO17(P0_12);
#endif

DigitalInOut _GPIO00(D2); // P0_19
DigitalInOut _GPIO01(D3); // P0_12
DigitalInOut _GPIO02(D4); // P0_18
DigitalInOut _GPIO03(D5); // P0_28
DigitalInOut _GPIO04(D6); // P0_16
DigitalInOut _GPIO05(D7); // P0_17
DigitalInOut _GPIO06(D8); // P0_13
DigitalInOut _GPIO07(D9); // P0_27
/** replace
DigitalInOut _GPIO00(P0_17);
DigitalInOut _GPIO01(P0_18);
DigitalInOut _GPIO02(P0_19);
DigitalInOut _GPIO03(P0_20);
DigitalInOut _GPIO04(P0_21);
DigitalInOut _GPIO05(P0_22);
DigitalInOut _GPIO06(P0_23);
DigitalInOut _GPIO07(P0_14);
*/

SPI _spi(D11, D12, D13); // mosi, miso, sclk
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    dev4.frequency(400000);//400k
#else
    DigitalInOut* gpio1[]={
        &_GPIO10,
        &_GPIO11,
        &_GPIO12,
        &_GPIO13,
        &_GPIO14,
        &_GPIO15,
        &_GPIO16,
        &_GPIO17,
    };
    for(int k=0; k<8; k++){
        gpio1[k]->input();
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    }
#endif
    DigitalInOut* gpio0[]={
        &_GPIO00,
        &_GPIO01,
        &_GPIO02,
        &_GPIO03,
        &_GPIO04,
        &_GPIO05,
        &_GPIO06,
        &_GPIO07,
    };
    for(int k=0; k<8; k++){
        gpio0[k]->input();
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
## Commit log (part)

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2015-01-05 ignore zip file
2015-01-05 [ NEW ] eagle setting files
2015-01-05 fiducials
2015-01-05 [ GERBER ] update
    panelized
2015-01-05 library update
2015-01-05 panelized as changed
2015-01-05 remove ignored files
2015-01-05 added BOM list
2015-01-06 setting file update
2015-01-06 [ SCH ] pullups moved
2015-01-06 Revert "Revert "via moved""
    This reverts commit 887c96878196973ea542345829e1096b9f4be77a.
2015-01-07 ignore pyc files
2015-01-07 ignore pyinstaller files
    ignore gui/dist and gui/build folders
2015-01-07 add new widget class
    created MyWidget class to make slot and signal functions
    copy and modify regWrite() from tempcommand/instr_local.py
2015-01-07 [ NEW ] pcb directory all PCB design files moved into pcb directory
2015-01-07 changed import and related to match pyinstaller issue pyinstaller2.2 fixes this issue(pip is still 2.1)
2015-01-08 [ GUI ] removed 0x prefix
2015-01-08 [ NEW ] Makefile
2015-01-08 import path added
2015-01-08 [ SUB ] mbed
2015-01-08 [ NEW ][ SUB ] tempcommand
2015-01-08 [ DEL ] python directory removed
    no more copying each time; use tempcommand submodule
2015-01-08 remove comment
2015-01-08 remove comments
2015-01-08 [ MERGE ] merge tempcommand/serial2i2c
    into python directory
2015-01-08 [ RENAME ] serial2i2c.py to tinyI2C.py
2015-01-08 update description
2015-01-09 update description
    no need to install mbed serial driver
2015-01-10 Revert "[ PCB ][ SCH ] BOM changed IC2: TPS76318(0.2A) -> TPS73618(0.4A) 296-15816-1-ND"
    This reverts commit bf9a7c92ce0625db0ef1a7f94382dcf04396bf4d.
2015-01-10 [ PCB ][ SCH ] BOM changed IC2: TPS76318 -> TPS73618
2015-01-11 [ PCB ][ BRD ] all pins on pin headers - added X5 for SWD - R1,R3,R4 moved
2015-01-11 [ PCB ][ SCH ][ BRD ] U1 replaced U1 is using mylib related trace change
2015-01-11 [ PCB ] U1 update as per library update
2015-01-11 [ PCB ] panelized as per update
2015-01-11 [ PCB ][ GERBER ] update
2015-01-13 [ PCB ][ BRD ] new header for ISP
    added ISP header next to RESET header
    removed trace to X1[3]
    moved R3 to near th header
    silkn name and bottom VDD trace change
2015-01-13 [ PCB ][ BRD ] LDO and buffer replace
    LDO replaced to MIC5355(Micron, 2 outputs, Vout1=3.3V, Vout2=1.8V) IC2
    -> IC3
    3.3V line added as LDO changed
    3-state buffer replaced from 1x quad to 2x single
    disconnect CTS, RTS
2015-01-13 [ PYTHON ] test program change
2015-01-13 [ PCB ][ BED ] new header X7 addition related move added silk for ISP/RST font size change: 1.0,1.2,1.3mm/15%
2015-01-14 [ PCB ][ BRD ] R and C library replace
    standard rcl to mylib
2015-01-14 [ PCB ][ SCH ] pull-up direction changed
2015-01-14 [ PCB ][ SCH ] X1[3] is now Vin(5V) [ BRD ] related tracechange
2015-01-15 [ MBED ][ LPC824 ] pinout matched to PCB
    pinout changed as PCB made
2015-01-15 [ PCB ][ SCH ] BOM update
2015-01-16 [ GUI ] layout change
2015-01-16 [ GUI ] layout change
    add registers and log message windows
2015-01-16 [ GUI ] layout change
    all spinboxes are 255 max
2015-01-16 [ GUI ][ NEW ] tinyI2Cgui.py
    applied recent gui change
2015-01-17 [ GUI ] default I2C slave address change(gui.py)
2015-01-18 [ GUI ] serial port selection bug fix
2015-01-19 [ GUI ] checkbox events added
2015-01-19 Revert "[ GUI ] hexSpinbox regular expression fix"
    This reverts commit f47c741ed80f932c771c0f988c5de0ce96ba1a1d.
2015-01-19 [ GUI ] GPIO UI change
    based on Qt design change
2015-01-20 [ GUI ][ Qt ] GPIO UI fix
    all registers are named
    UI changed to toggle button
2015-01-20 [ NEW ] Makefile.gui.bat
    batch file to generate python code
2015-01-20 [ GUI ] spec file / Makefile fix
2015-01-20 [ PYTHON ] test script change
2015-01-21 [ MBED ][ LPC824 ] ifdef switch TINYI2C
    ifdef switch between LPC824MAX and tinyI2C
2015-01-21 [ MBED ][ LPC824 ] returns ACK, NAK
    temporary use of P0_4/P0_0 for Serial
    returns "ACK" or "NAK" as per I2C communication result
2015-01-21 [ GUI ] I2CregRead() fix
    based on I2C response change
2015-01-21 [ PCB ][ BRD ] placement as per schematic change
2015-01-21 [ PCB ][ GERBER ] update based on brd fix 9037338ab0909b0d8c75574fc36787287275a06b
2015-01-22 [ PCB ][ SCH ] BOM update
    Q1 is 12MHz; CL for Q1(C8-9) = 18pF, 1005
2015-01-22 [ GUI ][ Qt ] set promotion for HexSpinBox
    QSpinBox'es who use HEX as data are promoted to be hexSpinbox.HexSpinBox
2015-01-22 [ GUI ] hexSpinbox.py and tinyI2Cgui.py fixes
    as ui file did
2015-01-22 [ PCB ][ SCH ][ NEW ] tinyI2C.sch.pdf
2015-01-22 [ PCB ][ GERBER ] update based on brd fix
2015-01-23 [ PYTHON ] test code change
2015-01-23 [ GUI ][ Qt ] default tab index
2015-01-27 [ GUI ] I2C_CONF, SPI_CONF registers
2015-01-27 [ MBED ][ LPC824 ] SPI register write fix
2015-01-28 [ GUI ][ NEW ] updateI2Cspeed(), updateSPIspeed()
2015-01-29 [ GUI ][ Qt ] I2C/ SPI registers
2015-01-29 [ GUI ][ RENAME ] updateI2C/SPI_speedTo/From()
    updateI2Cspeed() -> updateI2CspeedTo(), updateI2CspeedFrom()
    updateSPIspeed() -> updateSPIspeedTo(), updateSPIspeedFrom()
2015-02-02 [ GUI ][ Qt ] select polarity, packet length(SPI)
    now SPI register has ChipSelect porality(H/L active) and
    packet length information(8/16bit per packet)
2015-02-02 [ GUI ] SPI register sends CS POL and packet length
2015-02-02 [ GUI ] SPI packet length to be fixed 8 bit
    available 8/16 bits but fixed on GUI
2015-02-02 [ GUI ] I2C/SPI_CONF registers titled
2015-02-02 [ PCB ][ SCH ] IC3-NCs connection, silk fix IC3 = NCs are connected to GND silk = 0.2mm
2015-02-03 [ PCB ][ SCH ][ BRD ] add/replace GND testpad
    TP07R(0.7mm SMD pad) to 2x TPB1.27(1.27mm SMD pad)+0.8mm via
2015-02-03 [ PYTHON ] test code change
    E command related
2015-02-03 [ MBED ] formatting/ E command implement
2015-02-06 [ PCB ][ BRD ] U1 EP, 1.8V line
    U1 EP has changed to circle via
2015-02-17 [ PCB ][ SCH ] library update
    IC_LDO_MIC5355 updated
2015-02-17 [ PCB ][ BRD ] IC2/C1 moved; 1.8V line narrowed
    IC2: turned 90deg CW
    C1: moved to fit
    1.8V: narrowed; getting wider GND
2015-02-23 [ PCB ][ NEW ] BOM file
2015-02-25 [ PCB ] BOM fix
    semicolone to comma
2015-03-11 license update to CC-BY-SA
2015-05-22 Update and rename LICENSE to LICENSE.md
    ## creative commons
    # Attribution-NonCommercial-ShareAlike 4.0 International
2015-05-24 [ NEW ] PinOut drawings
    PinOut.pptx = a MS PowerPoint 2013 file
    TinyI2C_PinOut.png = a PNG generated from pptx
2015-05-24 Update README.md
    inline image
2015-06-14 [ FIX ] python
2015-08-25 [ PCB ] library update
2015-08-25 [ PCB ][ BRD ] V-CUT mark inserted
2015-08-29 [ PCB ] panel/drill size change, V-CUT mark, Panelize
2015-10-06 [ NEW ] tinyi2c_func.md
    relation list between macro on mbed source vs. enabled function
2015-10-06 fix to have better look
2015-10-06 [mbed] #warning to clarify board setting
2015-10-06 [mbed] add detail coments
2015-10-06 [mbed] function table moved to mbed/LPC824
2015-10-22 README.md update; more detailed information
2015-10-23 update README.md: register map and basic packet behavior
2015-10-23 update READMEs
2015-10-28 mbed/README.md updated
2015-11-06 README.md
2015-11-06 [ GUI ] Makefile, main.py, main.spec
2015-11-06 [ PYTHON ] .
2015-11-09 [ NEW ][ MBED ] Mercurial repository added
2015-11-26 update eagle version = 7.5.0; library update
2016-08-30 remove implements
2016-09-03 [ GUI ][ NEW ] tinyI2C.spec
    - spec file to compile GUI on Linux
2016-09-03 README.md: add GUI compile options
2016-09-03 [ GUI ] fix main.py - I2CregRead() error process
    - fix tinyI2C.spec
    - fix hexSpinbox.py
2016-09-03 rename mbed/ to doc/
2016-09-04 ignore executable building directories
2016-09-04 fix Makefile.in
2016-09-04 make-gui pre-builds python code for GUI
2016-09-04 [ GUI ] add error process for Windows serial port
    - for error of COM1-not-found error on windows
2016-09-04 Makefiles: make-gui stops if source is not changed
2016-09-04 [ GUI ] remove auto files/ obsolete files
    - auto files: *.spec, tinyI2Cgen.py
    - obsolete files: Makefile*.bat
2016-09-04 [ MBED ] update LPC1768 implements
2016-09-04 [ MBED ] LPC824 pinout changed
2016-09-04 Makefile: add pdf/tex/merge targets to generate pdf document
2016-09-04 doc/README.md: use piped table for multi lined cell
2016-09-09 [ NEW ] Sections 1 and 2 added
    - doc/TITLE.md: includes 1.0_tinyI2Cabstract.md
    - doc/data/commansSandP.csv: [NEW] S and P commands description table
    - doc/1.0_tinyI2Cabstract.md: [NEW] translating /README.md into two sections
2016-09-10 fix Makefile targets and dependencies
2016-09-10 fix section 1: fixes to include tables, title tables
2016-09-11 [ DOC ] fix section 1
2016-09-12 [ DOC ] MMDs' formattings
2016-09-12 add make-tex dependency to $(TARGET).md
2016-09-13 [ DOC ] add command R and W packet table
2016-09-14 rename commandSandP.csv -> commandSandP_wo.csv
2016-09-14 use daff.js(https://github.com/paulfitz/daff) for csv diff
2016-09-15 [ DOC ] hide contributor info for now
2016-09-15 [ DOC ] add python library API description
    - all python libraries use 0x30 as mask
    - add PythonAPI.md
    - TITLE.md imports PythonAPI.md
2016-09-15 [ DOC ] tailnote automation enabled
    - Makefile gets current git HEAD short hash
    - TITLE.md sets some more pandoc variables
2016-09-16 [ DOC ] edit Python API documentations
2016-09-17 [ DOC ] fix API descriptions
    section 1:
    - fix description for SPI function
    section 2:
    - making better look of tables
    python - reg_write():
    - fix default argument to use touple
2016-09-18 [ PYTHON ] fix a typo
2016-09-18 [ DOC ] apply changes in make-* rule
    - changes for related path
2016-09-18 [ DOC ] import PNG images, instead of tables, to make more visual waveforms
2016-09-19 add license declaration
2016-09-19 [ DOC ] update hardware list/command-E/commandRandW
2016-09-21 [ DOC ] simpler make targets
    - any of change in sources makes rebuild of html/pdf
    - $(MARKDOWN) lists all markdown (no matter if it is not listed in $(INPUT))
2016-09-22 [ DOC ] filename order change
    - 1.0 -> 1.0 [MOD]
    `> 2.0 [NEW]
    - 2.0 -> 3.0 [RENAME]
    - TITLE.md includes all of then in correct order
2016-09-22 [ DOC ] 2.0 remove comments
2016-09-25 ignore TeX template
2016-10-11 [ PYTHON ] apply autopep8
2016-10-16 [ PYTHON ] apply autopep8; fix test script
2016-10-19 fix register description typo in table; fix Command details
2016-10-25 fix non-printed character
    - character '>' did not appear to both html/pdf outputs unless back-quoted
2016-10-25 fix markdown files
2017-01-28 [ DOC ] start to point techbookfest(https://techbookfest.org) for publish
2017-01-30 [ DOC ] waveyaml files moved to data/waves
2017-01-30 [ DOC ] update document sources
2017-01-31 [ DOC ] start using bitfield for register description tables
    - register 0
    - register 1
2017-02-02 [ DOC ] update register description table titles
2017-02-03 [ DOC ] Nihongo Mendokusai
2017-02-05 [ DOC ] add pinout image (LPC11U35 version)
2017-02-11 book title renamed
2017-03-06 [ DOC ] document update
    - clean up comment outs
    - update pin out image
    - update API table style
2017-08-01 only $(MDDIR) requires override
2017-08-03 update table importer header
2017-08-06 upedate table includers
2017-08-06 update comment
2017-08-13 update ascii-hex table
2017-08-14 update yaml to use monospace font
2017-08-14 tex font config pre-defined in Makefile
2017-08-14 update sections 1 and 2
    - directry tree just uses code block
    - table-width is set
2017-08-20 update Makefile-s
    - Makefile.in no longer used
2017-09-17 set python/ importable
2017-09-17 bug fix in hex2ascii()
2017-09-17 GUI: apply autopep3
2017-10-01 GUI: use mask=0x30 to bypass encoding error
2017-10-01 apply autopep8
2017-10-01 rename filename to align with class name
2017-10-01 update README.md to alogn with py3 integration
2017-10-02 update ui builder command
2017-10-09 update shebang to point python3
2017-10-09 apply lib change
2017-10-16 stop using monospaced font
2017-10-16 update section 1
    - fix wrong list placement
2017-10-16 update tables
    - they are all quoted
2017-10-16 fix sections 1 and 9
2017-10-20 update section 9
2017-10-20 update section 2
    - change register listing order
